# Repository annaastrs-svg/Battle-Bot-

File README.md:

Laminax Bot 
---
Laminax is a battle bot with an axe-type weapon powered by an MG996R servo motor. 
It works thanks to an ESP32, controlled by a LogiTECH controller, and moves with two N20 motors. 
It's powered by 3 batteries (two 3.7V 500 mAh in parallel) & (one 3.7V 2000 mAh).

gemini made photos l o l , non modificated 

BTW look at my [JOURNAL.MD !](https://github.com/annaastrs-svg/Battle-Bot-/blob/actualizacion/journal.md)

[andd the youtube video of the project...](https://youtu.be/gHDkoSpJhSc?si=piYCwfSNSOPA8Sjc)may not be the best video its super homemade  ignore that...

How does it work?
How it’s controlled with a Logitech: you connect from the computer to the ESP32-C3's Wi-Fi and move the robot with the two joysticks. 
The trickiest part is the weapon—it moves with “A”; while you hold it, it attacks, and when you release the key, it goes back to its resting position.

CAD
---
Design - in the CAD there are the two DC motors, wheels, and two servomotors to give an idea of the layout

KiCAD
---
3D VIEW

Eschematic

CODE
---
Visual Studio Code
we have 3 codes
2 Python ones that are for testing the control and another for controlling the robot

[control test code](https://github.com/annaastrs-svg/Battle-Bot-/blob/actualizacion/Probar%20control.py)

[test control robot](https://github.com/annaastrs-svg/Battle-Bot-/blob/actualizacion/Control%20robot.py)

[Arduino IDE Code](https://github.com/annaastrs-svg/Battle-Bot-/blob/actualizacion/laminax_bot.ino)

# Bill of Materials (BOM)

| Component | Purpose | Qty | Price | Product |
|---|---|---|---|---|
| N20 Motors | Main motors (wheels) | 2 | $0.75 (kit of 2) | [2-Pack N20 Gear Motor Kit (30:1 / 298:1 / 150:1 / 50:1)](https://www.mercadolibre.com.mx/n20-micro-motor-dc-con-reduccion-6v-200-rpm/up/MLMU721988694?pdp_filters=item_id%3AMLM3286891636&from=gshop&matt_tool=15920969&matt_source=microsoft&matt_campaign_id=571305430&matt_ad_group_id=1177579225794197&matt_match_type=e&matt_network=o&matt_device=c&matt_merchant_id=50038545&matt_product_id=MLMU721988694&matt_product_partition_id=4577198197450204&matt_target_id=pla-4577198197450204&msclkid=cf92e911e1ec13565a9f83775c3f8272&utm_source=bing&utm_medium=cpc&utm_campaign=MLM_ML_BING_AO_CE-ALL-ALL_X_PLA_ALLB_TXS_ALL&utm_term=4577198197450204&utm_content=CE) |
| MG996R | Weapon servo motor | 1 | $7.50 | [MG996R Servo Motor](https://www.mercadolibre.com.mx/servomotor-mg996r--mg995-servo-motor/up/MLMU698938548?pdp_filters=item_id%3AMLM5005746376&from=gshop&matt_tool=15920969&matt_source=microsoft&matt_campaign_id=571305430&matt_ad_group_id=1177579225794197&matt_match_type=e&matt_network=o&matt_device=c&matt_merchant_id=50038545&matt_product_id=MLMU698938548&matt_product_partition_id=4577198197450206&matt_target_id=pla-4577198197450206&msclkid=b9da9ea54f45191d3b03f4c3f2cf8dbb&utm_source=bing&utm_medium=cpc&utm_campaign=MLM_ML_BING_AO_CE-ALL-ALL_X_PLA_ALLB_TXS_ALL&utm_term=4577198197450206&utm_content=CE) |
| ESP32-C3 SuperMini | Main controller (brain) | 1 | $0.32 | [ESP32-C3 SuperMini (WiFi + Bluetooth)](https://www.mercadolibre.com.mx/esp32-c3-esp32-supermini-wifi-bluetooth/p/MLM46912341?pdp_filters=item_id%3AMLM2779591141&from=gshop&matt_tool=15920969&matt_source=microsoft&matt_campaign_id=571305430&matt_ad_group_id=1177579225794197&matt_match_type=e&matt_network=o&matt_device=c&matt_merchant_id=50038545&matt_product_id=MLM46912341-product&matt_product_partition_id=4577198197450204&matt_target_id=pla-4577198197450204&msclkid=bb5ca1be34e817af15f1cbd88904733f&utm_source=bing&utm_medium=cpc&utm_campaign=MLM_ML_BING_AO_CE-ALL-ALL_X_PLA_ALLB_TXS_ALL&utm_term=4577198197450204&utm_content=CE) |
| 3.7V 2000mAh Battery | Power for ESP32/Servo | 1 | $2.29 | |
| Dupont Jumper Wire Kit | Wiring | 1 | $0.31 | [Dupont Jumper Wires, M-M, 20cm (40-pack)](https://www.mercadolibre.com.mx/cables-jumper-dupont-m-m-20cm-40-arduino-protoboard/p/MLM46898481?pdp_filters=item_id%3AMLM3587883832&from=gshop&matt_tool=15920969&matt_source=microsoft&matt_campaign_id=571305430&matt_ad_group_id=1177579225794197&matt_match_type=e&matt_network=o&matt_device=c&matt_merchant_id=50038545&matt_product_id=MLM46898481-product&matt_product_partition_id=4577198197450205&matt_target_id=pla-4577198197450205&msclkid=0b59b00f2e4e12d6929bda69904acc84&utm_source=bing&utm_medium=cpc&utm_campaign=MLM_ML_BING_AO_CE-ALL-ALL_X_PLA_ALLB_TXS_ALL&utm_term=4577198197450205&utm_content=CE) |
| 3.7V 500mAh Battery | Power for motors | 2 | ~$3.00 ea. | [3.7V 500mAh LiPo Battery (1S, 25C)](https://www.mercadolibre.com.mx/bateria-lipo-litio-37v-500mah-recargable-1s-25c-pila-litio/p/MLM2039836242) |
| DRV8833 | H-bridge (motor driver) | 1 | $55.00 | [DRV8833 Motor Driver Module](https://www.electronicsavalanche.com.mx/shop/driv001-modulo-drv8833-driver-para-motores-890) |

**Estimated Total: ~$20.35 USD**

# Conecction table

| Componente | Pin | → | Componente | Pin |
|---|---|---|---|---|
| ESP32 | 5 | → | Servo | S |
| ESP32 | 0 | → | DRV8833 | IN1 |
| ESP32 | 1 | → | DRV8833 | IN2 |
| ESP32 | 2 | → | DRV8833 | IN3 |
| ESP32 | 3 | → | DRV8833 | IN4 |
| ESP32 | GND | → | Protoboard | GND COMÚN |
| ESP32 | 5V | → | Protoboard | 5V |
| DRV8833 | GND | → | Protoboard | GND COMÚN |
| DRV8833 | SLEEP | → | Protoboard | 5V |
| DRV8833 | 5V (VM) | → | Protoboard | DIRECTA  |
| DRV8833 | OUT1 | → | Motor A | terminal |
| DRV8833 | OUT2 | → | Motor A | terminal |
| DRV8833 | OUT3 | → | Motor B | terminal |
| DRV8833 | OUT4 | → | Motor B | terminal |
| Servo | 5V | → | Protoboard | 5V |
| Servo | GND | → | Protoboard | GND COMÚN |
| Baterías (paralelo) | negativo | → | Protoboard | GND COMÚN |
| Baterías (paralelo) | positivo | → | Protoboard | DIRECTA  |
| Baterías serie | negativo | → | Protoboard | GND COMÚN |
| Batería serie | positivo | → | Protoboard | 5V |

Notes
---
Justification of the hours:
The project had 2 total changes, in the CAD, in the code, and materials. This made the project take longer.

This project was made for [MACONDO](https://macondo.hackclub.com/dashboard)

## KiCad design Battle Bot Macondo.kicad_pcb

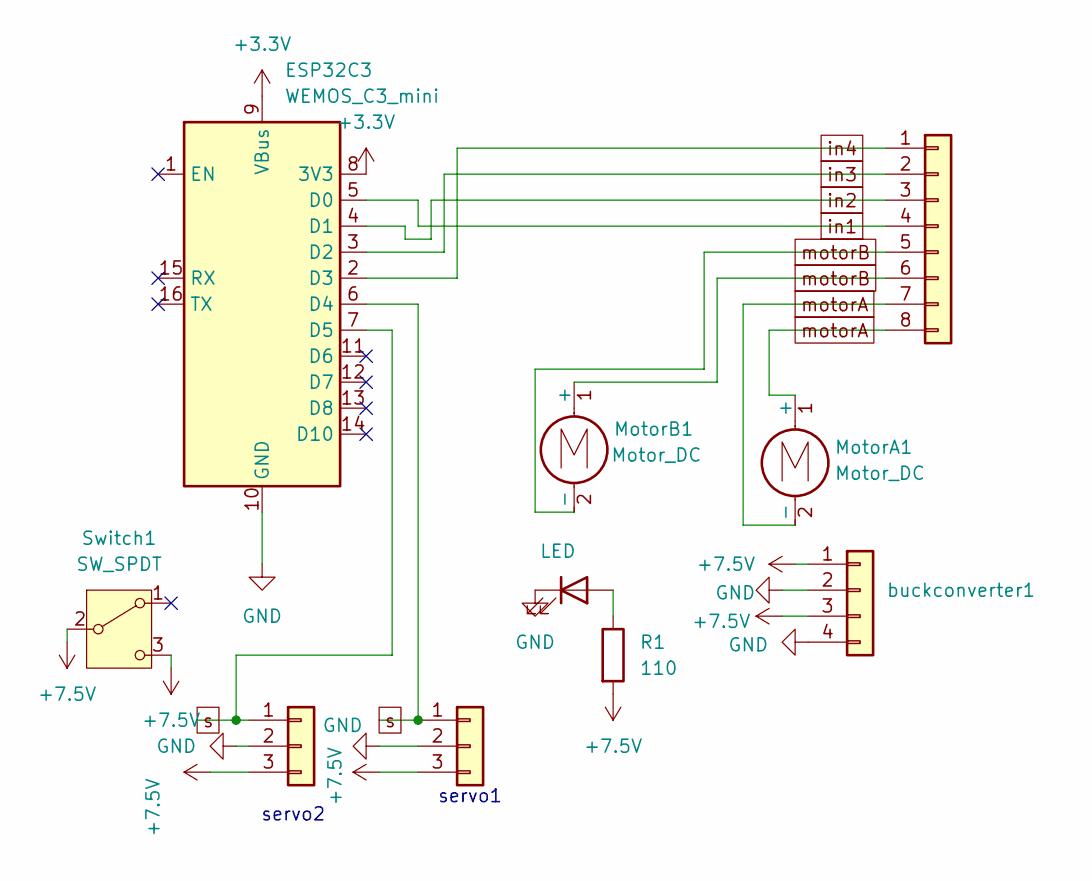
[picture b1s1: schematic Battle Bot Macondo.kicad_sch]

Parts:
D1: LED; LED_D5.0mm
ESP32C3: WEMOS_C3_mini
MotorA1: Motor_DC; TerminalBlock_MaiXu_MX126-5.0-02P_1x02_P5.00mm
MotorB1: Motor_DC; TerminalBlock_MaiXu_MX126-5.0-02P_1x02_P5.00mm
PuenteH1: Conn_01x08; PinSocket_1x08_P2.54mm_Vertical
R1: 110; R_Axial_DIN0207_L6.3mm_D2.5mm_P10.16mm_Horizontal
Switch1: SW_SPDT; PinHeader_1x03_P2.54mm_Horizontal
buckconverter1: Conn_01x04; PinSocket_1x04_P2.54mm_Vertical
servo2: Conn_01x03; PinHeader_1x03_P2.54mm_Vertical
servomotor1: Conn_01x03; PinHeader_1x03_P2.54mm_Vertical

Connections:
+3.3V: ESP32C3.8 (3V3), ESP32C3.9 (VBus)
+7.5V: R1.2, Switch1.2 (B), Switch1.3 (C), buckconverter1.1, buckconverter1.3, servo2.3, servomotor1.3
GND: D1.1 (K), ESP32C3.10 (GND), buckconverter1.2, buckconverter1.4, servo2.2, servomotor1.2
unnamed: D1.2 (A), R1.1
in1: ESP32C3.5 (D0), PuenteH1.4
in2: ESP32C3.4 (D1), PuenteH1.3
in3: ESP32C3.3 (D2), PuenteH1.2
in4: ESP32C3.2 (D3), PuenteH1.1
motorA: MotorA1.1 (+), MotorA1.2 (-), PuenteH1.7, PuenteH1.8
motorB: MotorB1.1 (+), MotorB1.2 (-), PuenteH1.5, PuenteH1.6
s: ESP32C3.6 (D4), ESP32C3.7 (D5), servo2.1, servomotor1.1

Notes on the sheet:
servo2
servo1

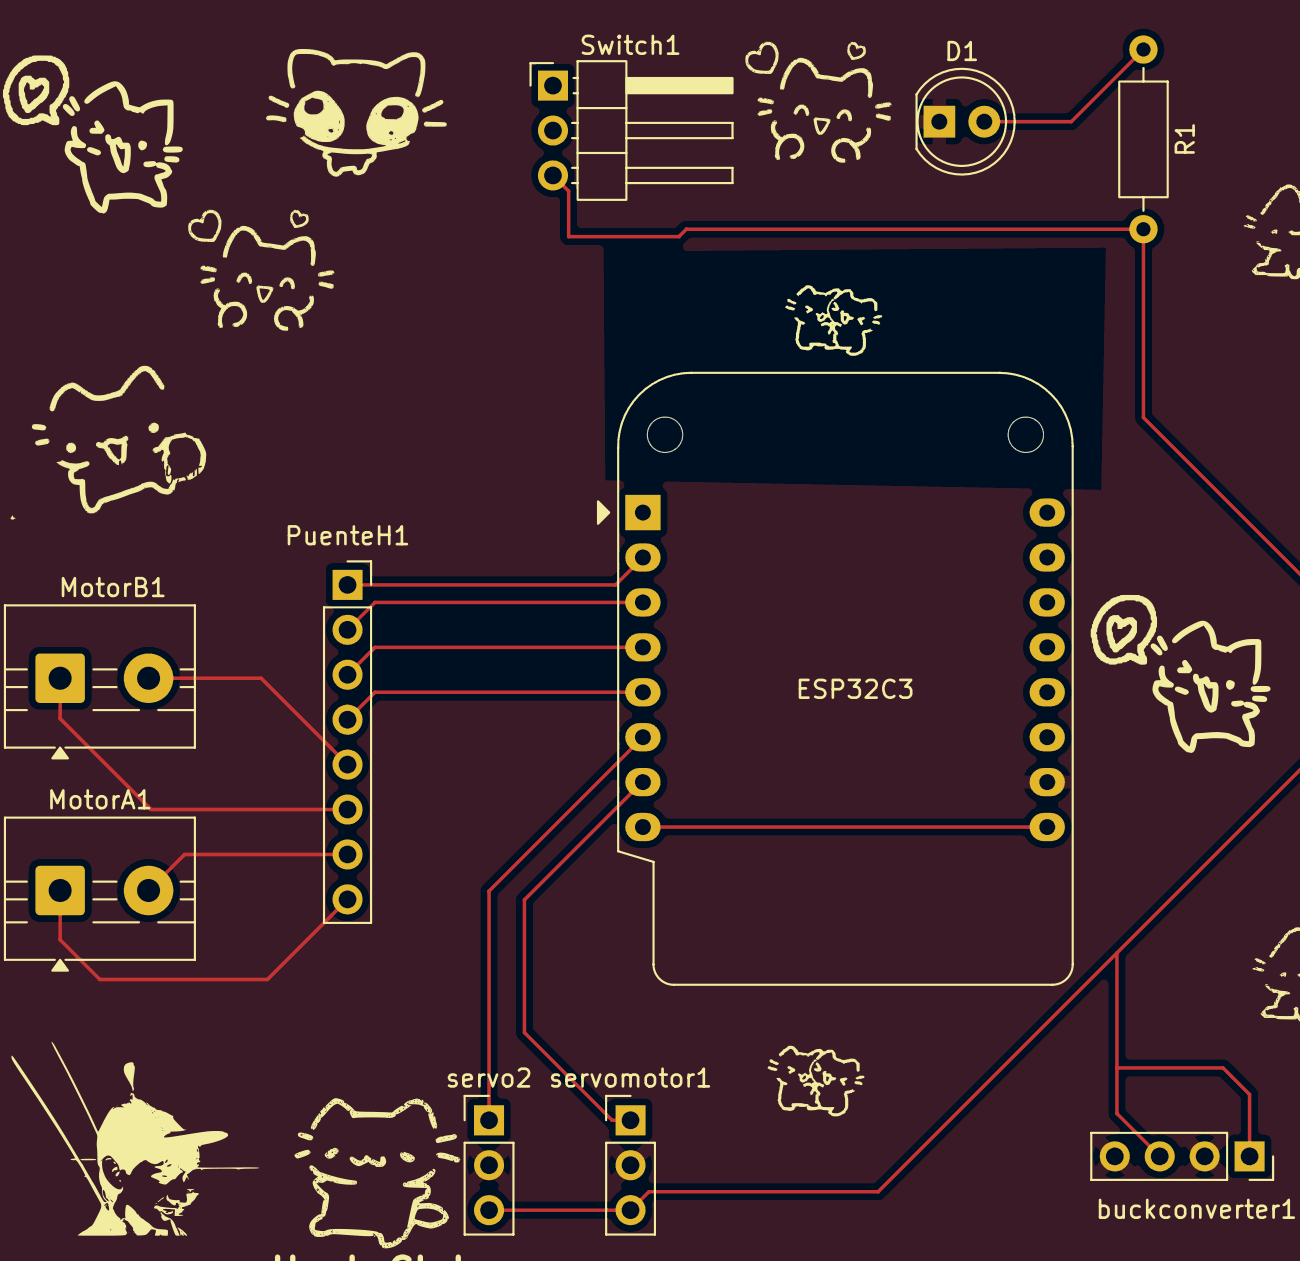
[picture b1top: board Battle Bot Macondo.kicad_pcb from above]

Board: 2 copper layers, 11 parts (0 on the bottom side), 11 nets.

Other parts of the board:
Hack Club : LOGO; me
